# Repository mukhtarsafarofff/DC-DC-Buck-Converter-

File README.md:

(DEU)   Ein Konstantstrom (CC)- und Konstantspannungs (CV)-Wandler können in verschiedenen Situationen äußerst nützlich sein. Wenn Sie beispielsweise eine Lithiumbatterie mit einem konstanten Strom laden möchten, können Sie dies mit diesem Modul sehr einfach tun. Darüber hinaus wird empfohlen, bei der ersten Inbetriebnahme einer Schaltung immer einen konstanten Strom zu verwenden, um Schäden an Ihrer Schaltung zu begrenzen, falls Sie während des Aufbauprozesses Fehler gemacht haben.Ich habe zwei 10K-Potentiometer, die verwendet werden, um den konstanten Strom- und Spannungspegel einzustellen. Darüber hinaus gibt es drei LED-Anzeigen auf der Platine; die erste in der Nähe des Eingangsanschlusses zeigt an, wenn das Modul im Konstantstrommodus ist, während die anderen beiden in der Nähe des Ausgangs hauptsächlich für Batterieladeanwendungen sind (Batterielade- und Batterievollanzeige). Abgesehen davon hat dieser IC einen Eingangsspannungsbereich von 8V bis 36V, und die Ausgangsspannung des Geräts beträgt 1,25V bis 32V. Bei maximaler Belastung kann das PWM des Geräts eine Tastverhältnis von 100% erreichen und es kann bei einer Betriebsfrequenz von 180 kHz arbeiten. Der konstante Ausgangsstrom des Moduls beträgt 5A und es kann bis zu 96% Effizienz erreichen, während es arbeitet. Wenn wir über Schutzfunktionen sprechen, verfügt es über thermischen Überlastschutz, Kurzschlussschutz und Funktion zur Strombegrenzung.Das Hauptkomponente auf dieser Platine ist der XL4015-Buck-Wandler-IC, ein 5-poliger IC, der entworfen wurde.Wenn wir über Schutzfunktionen sprechen, verfügt es über thermischen Überlastschutz, Kurzschlussschutz und Funktion zur Strombegrenzung. Die Hauptkomponente auf dieser Platine ist der XL4015-Buck-Wandler-IC, ein 5-poliger IC, der entworfen wurde. Im Schaltbild haben wir einen 78L05-Spannungsregler, der ein ultra-niedriger Leistungsregler ist, der verwendet wird, um die Eingangsspannung auf konstante 5V für den TL431-IC umzuwandeln. Der TL431 ist eine Referenz, die mit Hilfe eines 71,5K-Widerstands und eines Potentiometers auf den konstanten Stromreglermodus eingestellt ist. Diese Referenz wird mit der Sensorspannung von der Ausgangsseite des Widerstands verglichen, um den Strom zu begrenzen.  Die Schaltung unten ist die TL431-Schaltung, die eine konstante Stromquelle für die Operationsverstärker bereitstellt. Wenn die Batterie vollständig aufgeladen ist, wird der Ausgang niedrig, sodass die Lade-LED aufleuchtet. Wenn eine Batterie geladen wird, leuchtet die andere LED auf, um anzuzeigen, dass die Batterie geladen wird.  Ich habe zunächst das Buck-Wandler-Modul an die Stromversorgung angeschlossen und den Ausgang an die Gleichstromlast angeschlossen.

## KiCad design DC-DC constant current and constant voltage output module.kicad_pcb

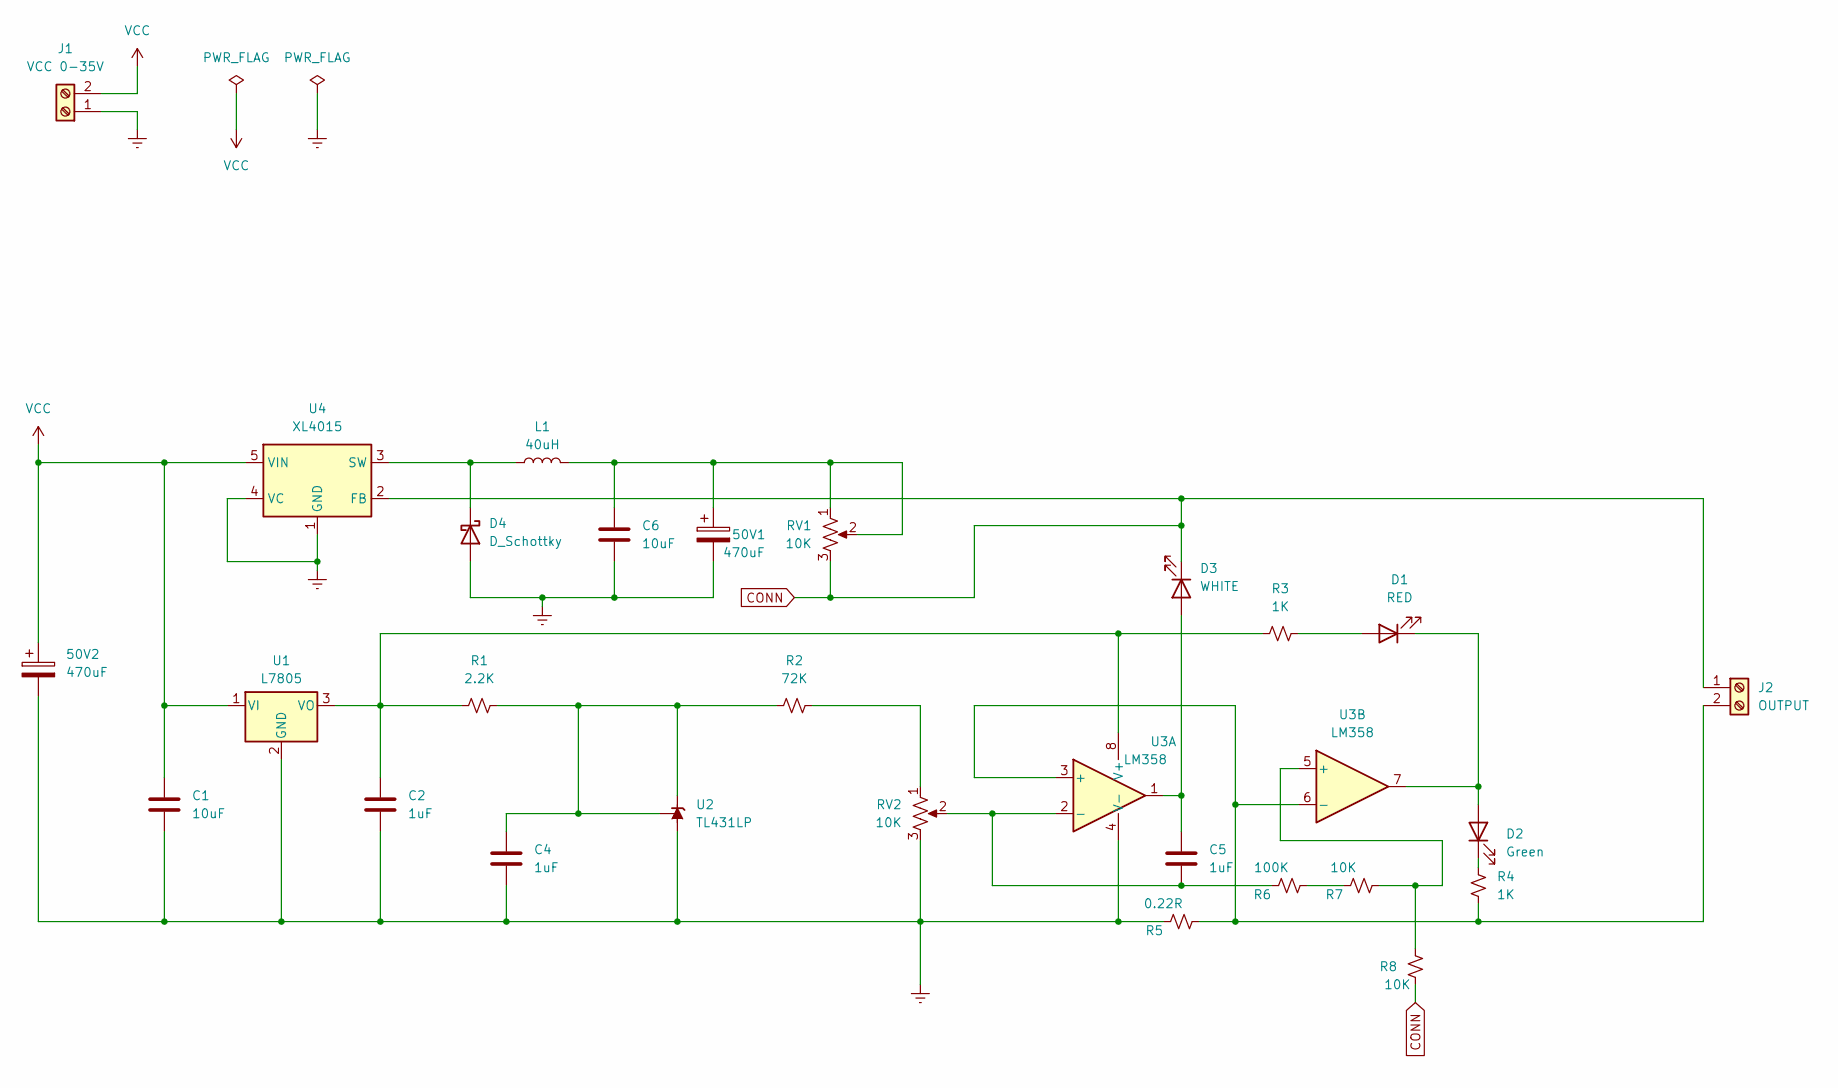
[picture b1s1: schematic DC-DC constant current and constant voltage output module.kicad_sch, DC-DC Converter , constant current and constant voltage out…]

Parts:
50V1, 50V2: 470uF; CP_Radial_D12.5mm_P7.50mm
C1, C6: 10uF; C_Disc_D8.0mm_W5.0mm_P7.50mm
C2, C4, C5: 1uF; C_Disc_D8.0mm_W5.0mm_P7.50mm
D1: RED; LED_D5.0mm
D2: Green; LED_D5.0mm_Clear
D3: WHITE; LED_D3.0mm_Horizontal_O3.81mm_Z6.0mm
D4: D_Schottky; D_T-1_P10.16mm_Horizontal
J1: VCC 0-35V; TerminalBlock_bornier-2_P5.08mm
J2: OUTPUT; TerminalBlock_bornier-2_P5.08mm
L1: 40uH; L_Toroid_Horizontal_D17.3mm_P15.24mm_Bourns_2000
R1: 2.2K; R_Axial_DIN0309_L9.0mm_D3.2mm_P12.70mm_Horizontal
R2: 72K; R_Axial_DIN0309_L9.0mm_D3.2mm_P12.70mm_Horizontal
R3, R4: 1K; R_Axial_DIN0309_L9.0mm_D3.2mm_P12.70mm_Horizontal
R5: 0.22R; R_Axial_DIN0309_L9.0mm_D3.2mm_P12.70mm_Horizontal
R6: 100K; R_Axial_DIN0309_L9.0mm_D3.2mm_P12.70mm_Horizontal
R7, R8: 10K; R_Axial_DIN0309_L9.0mm_D3.2mm_P12.70mm_Horizontal
RV1, RV2: 10K; Potentiometer_Vishay_148-149_Single_Horizontal
U1: L7805; TO-220-3_Vertical
U2: TL431LP; TO-92_Inline
U3: LM358; DIP-8-16_W7.62mm
U4: XL4015; TO-263-5_TabPin3

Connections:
CONN: D3.1 (K), J2.1, R8.1, RV1.3, U4.2 (FB)
Earth: 50V1.2, 50V2.2, C1.2, C2.2, C4.2, C6.2, D4.2 (A), J1.1, R5.1, RV2.3, U1.2 (GND), U2.2 (A), U3.4 (V-), U4.1 (GND), U4.4 (VC)
unnamed: 50V1.1, C6.1, L1.2, RV1.1, RV1.2
unnamed: D1.2 (A), R3.2
unnamed: D1.1 (K), D2.2 (A), U3.7
unnamed: D2.1 (K), R4.2
unnamed: C5.1, D3.2 (A), U3.1
unnamed: D4.1 (K), L1.1, U4.3 (SW)
unnamed: J2.2, R4.1, R5.2, U3.3 (+), U3.6 (-)
unnamed: R2.2, RV2.1
unnamed: R6.2, R7.1
unnamed: C2.1, R1.1, R3.1, U1.3 (VO), U3.8 (V+)
unnamed: C4.1, R1.2, R2.1, U2.1 (REF), U2.3 (K)
unnamed: C5.2, R6.1, RV2.2, U3.2 (-)
unnamed: R7.2, R8.2, U3.5 (+)
VCC: 50V2.1, C1.1, J1.2, U1.1 (VI), U4.5 (VIN)

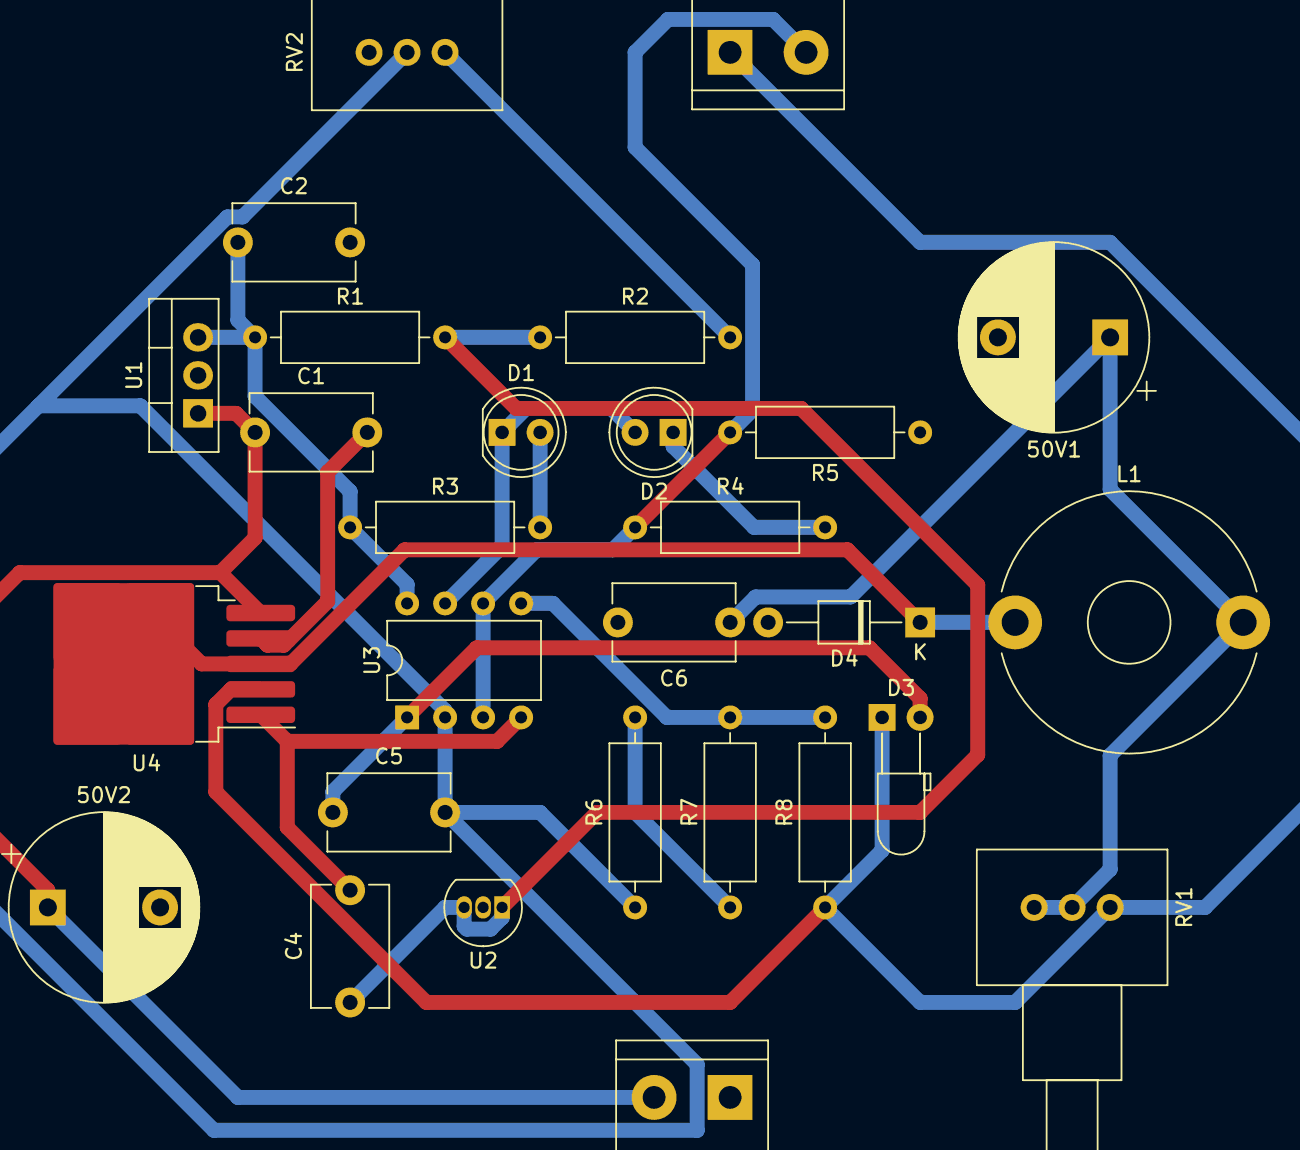
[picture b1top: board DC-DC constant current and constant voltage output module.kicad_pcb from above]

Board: 2 copper layers, 28 parts (0 on the bottom side), 16 nets.

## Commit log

2024-03-29 DC-DC buck Converter is accomplished
